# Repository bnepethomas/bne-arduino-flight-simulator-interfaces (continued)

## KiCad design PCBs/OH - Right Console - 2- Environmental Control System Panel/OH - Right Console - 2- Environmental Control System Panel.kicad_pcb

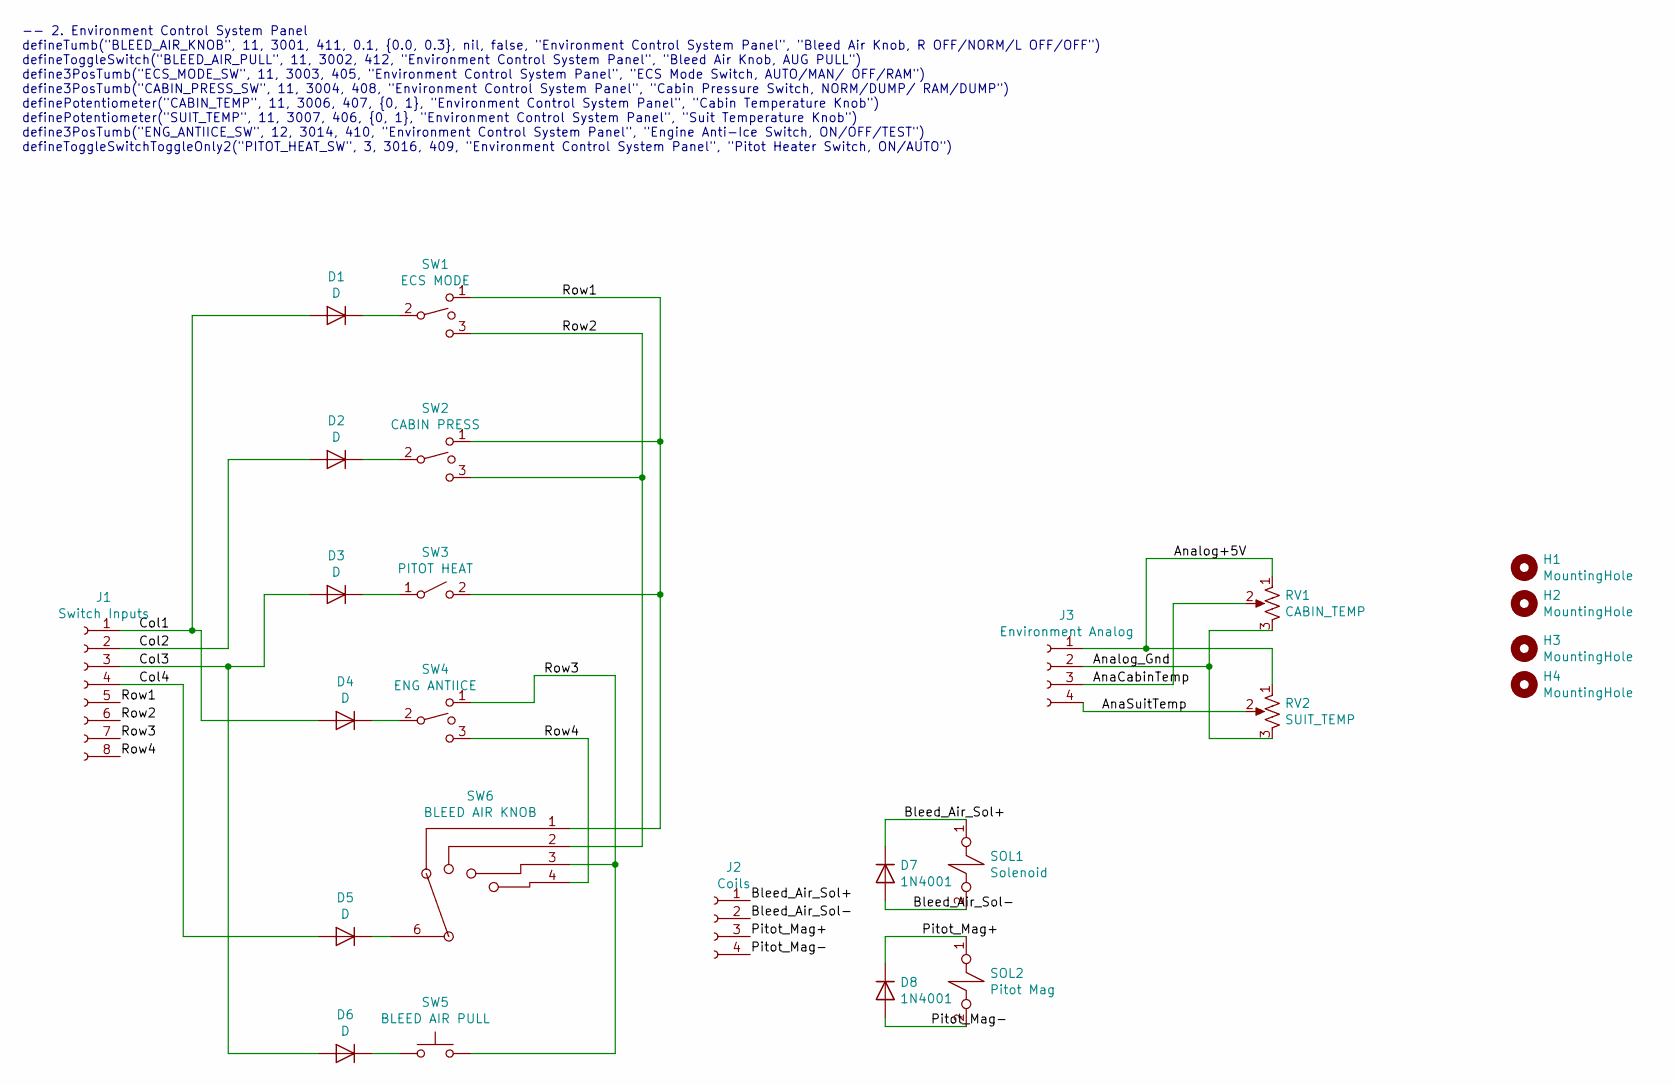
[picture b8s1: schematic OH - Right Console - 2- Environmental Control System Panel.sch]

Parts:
D1, D2, D3, D4, D5, D6: D; D_Signal_P7.62mm_Horizontal
D7, D8: 1N4001; D_DO-41_SOD81_P10.16mm_Horizontal
H1, H2, H3, H4: MountingHole; MountingHole_3.2mm_M3
J1: Switch Inputs; Molex_1x08_P2.54mm_Vertical
J2: Coils; Molex_1x04_P2.54mm_Vertical
J3: Environment Analog; Molex_1x04_P2.54mm_Vertical
RV1: CABIN_TEMP; Molex_1x03_P2.54mm_Vertical
RV2: SUIT_TEMP; Molex_1x03_P2.54mm_Vertical
SOL1: Solenoid; Molex_1x02_P2.54mm_Vertical
SOL2: Pitot Mag; Molex_1x02_P2.54mm_Vertical
SW1: ECS MODE; Molex_1x03_P2.54mm_Vertical
SW2: CABIN PRESS; Molex_1x03_P2.54mm_Vertical
SW3: PITOT HEAT; Molex_1x02_P2.54mm_Vertical
SW4: ENG ANTIICE; Molex_1x03_P2.54mm_Vertical
SW5: BLEED AIR PULL; Molex_1x02_P2.54mm_Vertical
SW6: BLEED AIR KNOB; Molex_1x06_P2.54mm_Vertical

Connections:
/AnaCabinTemp: J3.3, RV1.2
/AnaSuitTemp: J3.4, RV2.2
/Analog+5V: J3.1, RV1.1, RV2.1
/Analog_Gnd: J3.2, RV1.3, RV2.3
/Bleed_Air_Sol+: D7.1 (K), J2.1, SOL1.1
/Bleed_Air_Sol-: D7.2 (A), J2.2, SOL1.2
/Col1: D1.2 (A), D4.2 (A), J1.1
/Col2: D2.2 (A), J1.2
/Col3: D3.2 (A), D6.2 (A), J1.3
/Col4: D5.2 (A), J1.4
/Pitot_Mag+: D8.1 (K), J2.3, SOL2.1
/Pitot_Mag-: D8.2 (A), J2.4, SOL2.2
/Row1: J1.5, SW1.1, SW2.1, SW3.2 (B), SW6.1
/Row2: J1.6, SW1.3, SW2.3, SW6.2
/Row3: J1.7, SW4.1, SW5.2, SW6.3
/Row4: J1.8, SW4.3, SW6.4
unnamed: D1.1 (K), SW1.2
unnamed: D2.1 (K), SW2.2
unnamed: D3.1 (K), SW3.1 (A)
unnamed: D4.1 (K), SW4.2
unnamed: D5.1 (K), SW6.6 (COM)
unnamed: D6.1 (K), SW5.1

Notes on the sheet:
-- 2. Environment Control System Panel defineTumb("BLEED_AIR_KNOB", 11, 3001, 411, 0.1, {0.0, 0.3}, nil, false, "Environment Control System Panel", "Bleed Air Knob, R OFF/NORM/L OFF/OFF") defineToggleSwitch("BLEED_AIR_PULL", 11, 3002, 412, "Environment Control System Panel", "Bleed Air Knob, AUG PU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

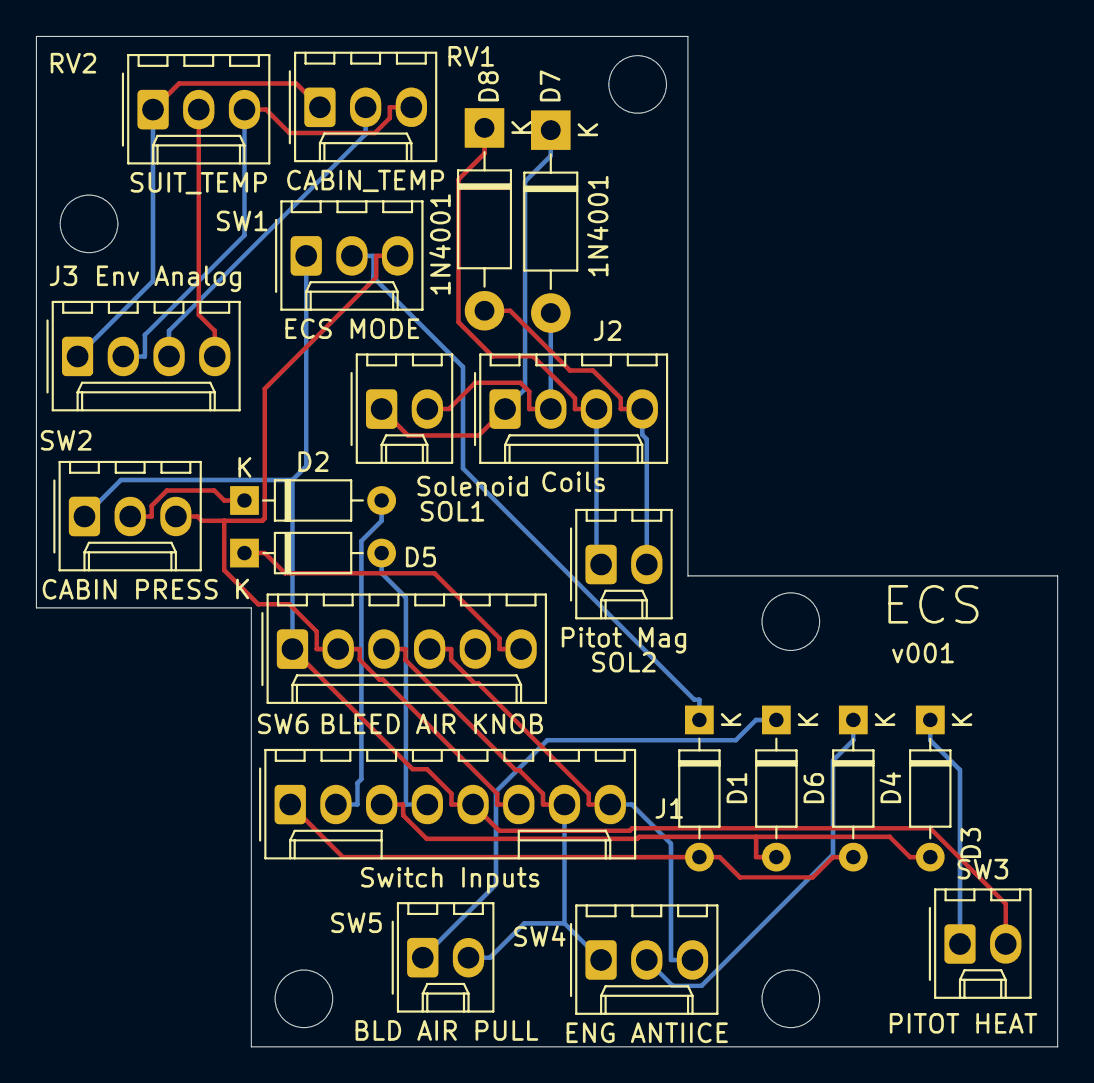
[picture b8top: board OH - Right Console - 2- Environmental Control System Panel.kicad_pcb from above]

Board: 2 copper layers, 56.7 x 56.1 mm, 26 parts (0 on the bottom side), 22 nets.

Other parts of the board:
H5: MountingHole; MountingHole_3.2mm_M3
